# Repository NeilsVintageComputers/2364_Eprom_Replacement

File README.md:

# 2364_Eprom_Replacement

These adapters mount a smd eeprom, AT28C64B, on a pcb that fits and plugs into the 24-pin 2364 footprint. It is much narrower than all the other adapters I have seen (only as wide as the 2364 socket) which allows them to fit side by side in closely spaced sockets like in the IBM 5150.

The programming adapters that are required to program the eeprom board have a 28 or 32 pin header to plug into a eprom programmer.

The only difference in the two versions is the number of pins on the programming adapter, one has 32 pins which is the number of pins on the smd version of the AT28C64B, the other has 28 pins which is the number of pins on the dil version of the AT28C64.  
Choose which ever version will suit your eprom programmer, if the programmer supports the 32-pin SMD version build the 32-pin adapter or if it only supports the 28-pin throughhole version then build the 28-pin adapter.

The jumpers on the rear should be OPEN when programming the device, CLOSED for use in normal read mode.
The "A" and "B" (Which is NOT a jumper) on the eeprom board should be connected to "A" and "B" on the programmer board.

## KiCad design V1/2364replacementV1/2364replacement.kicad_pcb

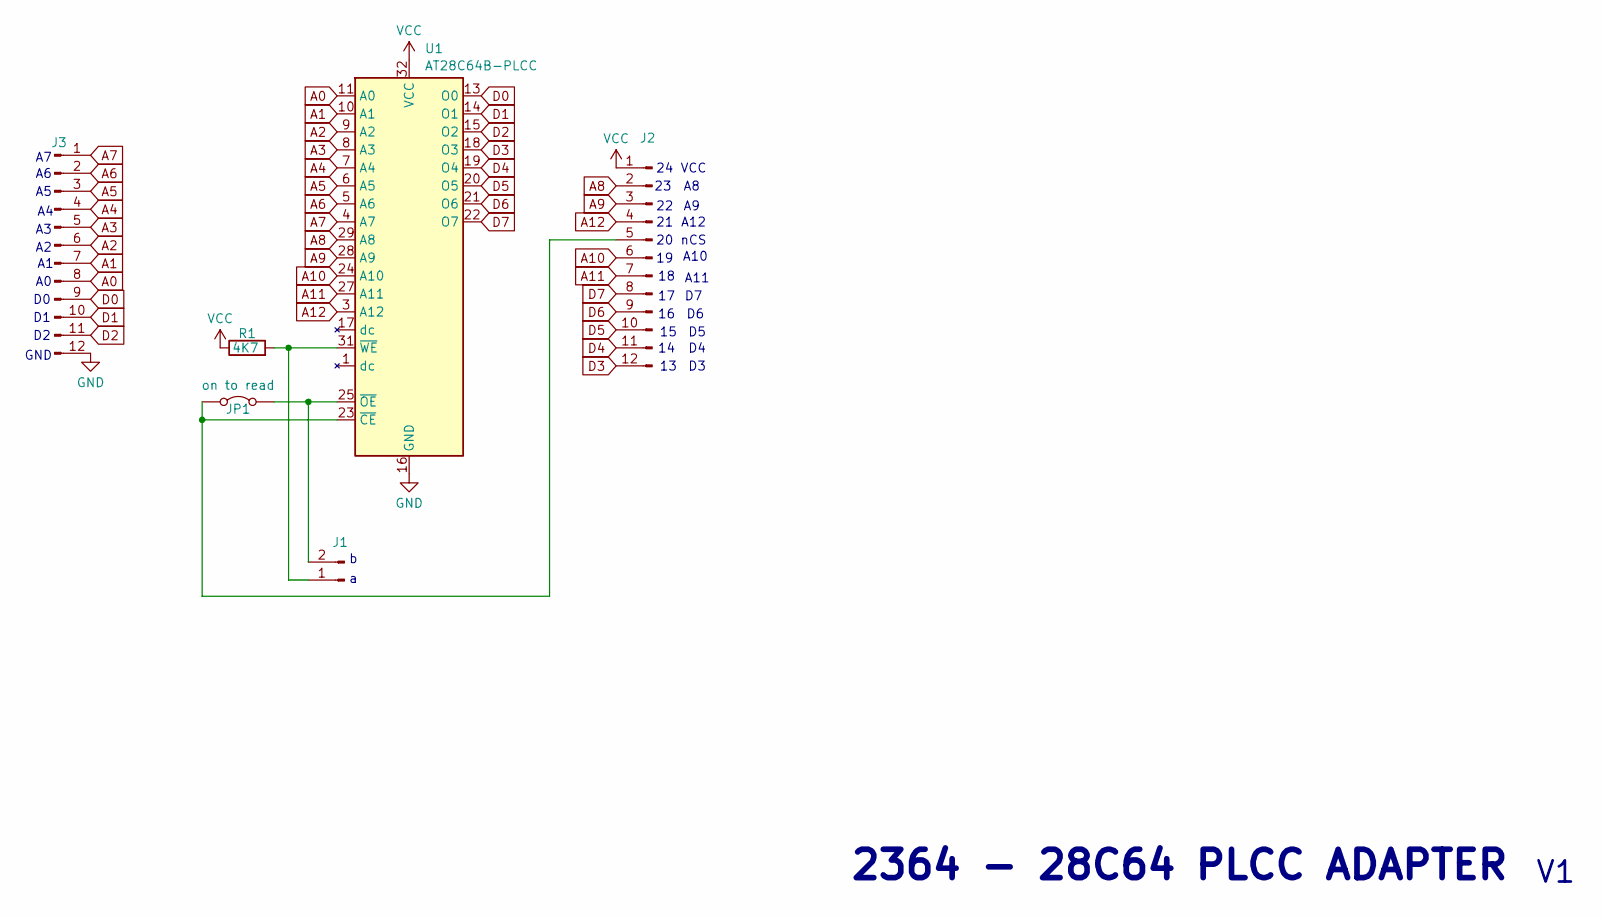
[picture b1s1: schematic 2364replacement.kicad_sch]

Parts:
J1: Conn_01x02_Pin; PinHeader_1x02_P2.54mm_Vertical
J2, J3: Conn_01x12_Pin; PinHeader_1x12_P2.54mm_Vertical
JP1: on to read; PinHeader_1x02_P2.54mm_Vertical
R1: 4K7; R_Axial_DIN0207_L6.3mm_D2.5mm_P10.16mm_Horizontal
U1: AT28C64B-PLCC; PLCC-32_11.4x14.0mm_P1.27mm

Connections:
A0: J3.8, U1.11 (A0)
A1: J3.7, U1.10 (A1)
A2: J3.6, U1.9 (A2)
A3: J3.5, U1.8 (A3)
A4: J3.4, U1.7 (A4)
A5: J3.3, U1.6 (A5)
A6: J3.2, U1.5 (A6)
A7: J3.1, U1.4 (A7)
A8: J2.2, U1.29 (A8)
A9: J2.3, U1.28 (A9)
A10: J2.6, U1.24 (A10)
A11: J2.7, U1.27 (A11)
A12: J2.4, U1.3 (A12)
D0: J3.9, U1.13 (O0)
D1: J3.10, U1.14 (O1)
D2: J3.11, U1.15 (O2)
D3: J2.12, U1.18 (O3)
D4: J2.11, U1.19 (O4)
D5: J2.10, U1.20 (O5)
D6: J2.9, U1.21 (O6)
D7: J2.8, U1.22 (O7)
GND: J3.12, U1.16 (GND)
unnamed: J2.5, JP1.1 (A), U1.23 (~CE)
unnamed: J1.1, R1.2, U1.31 (~WE)
unnamed: J1.2, JP1.2 (B), U1.25 (~OE)
VCC: J2.1, R1.1, U1.32 (VCC)

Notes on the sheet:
VCC
A12
nCS
A10
2364 - 28C64 PLCC ADAPTER
A11
GND

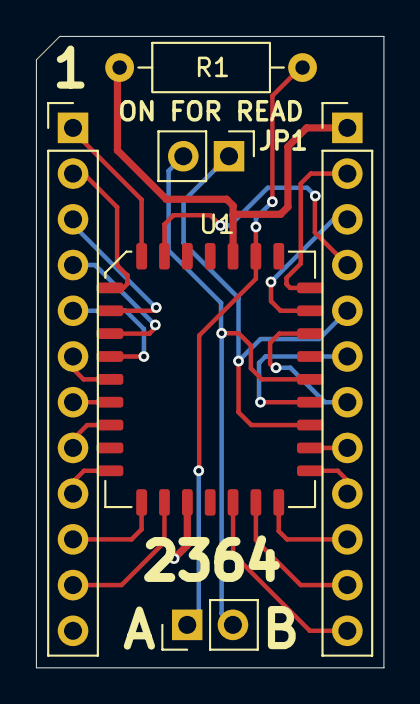
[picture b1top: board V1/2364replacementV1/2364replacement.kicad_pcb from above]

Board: 2 copper layers, 19.3 x 35.1 mm, 6 parts (0 on the bottom side), 26 nets.

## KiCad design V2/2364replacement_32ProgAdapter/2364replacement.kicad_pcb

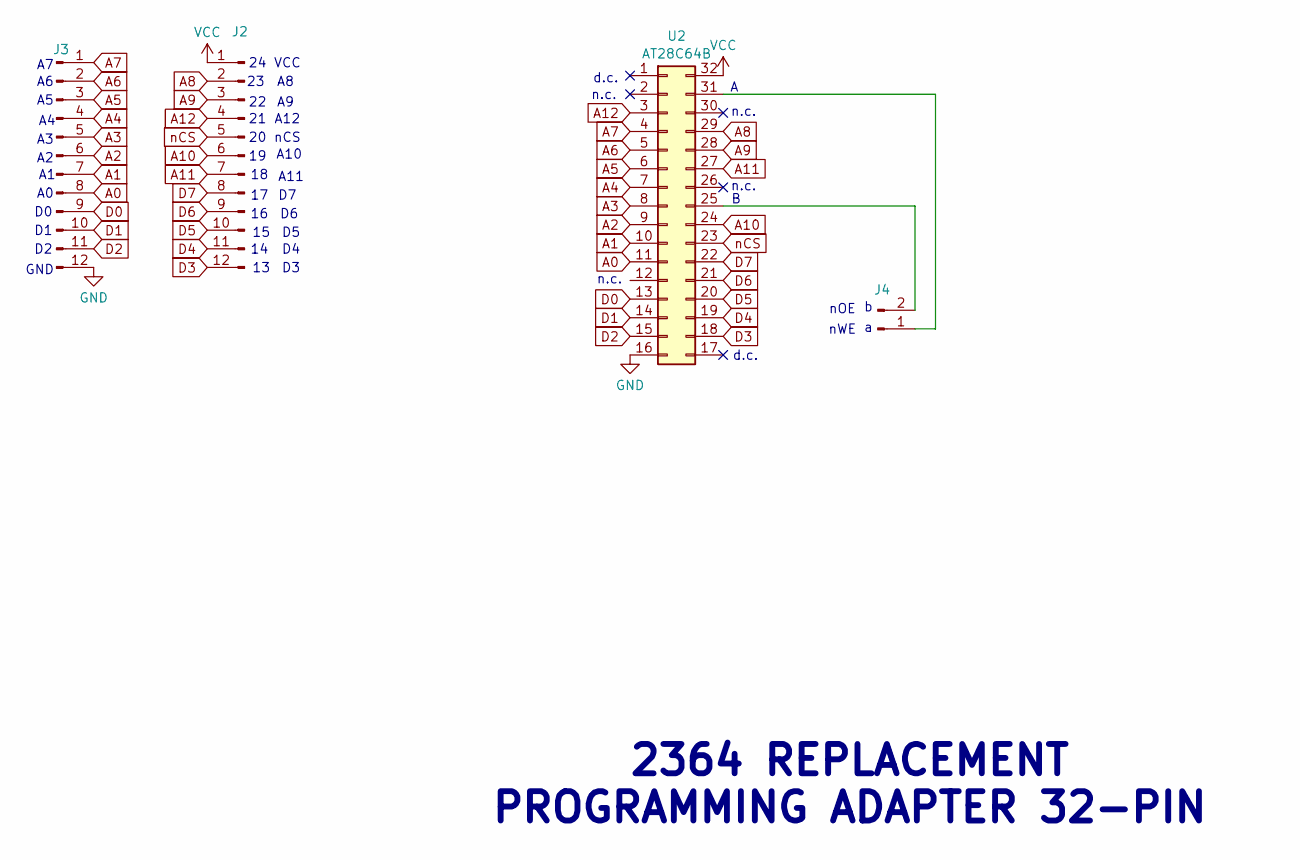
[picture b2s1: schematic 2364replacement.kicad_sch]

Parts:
J2, J3: Conn_01x12_Pin; PinHeader_1x12_P2.54mm_Vertical
J4: Conn_01x02_Pin; PinHeader_1x02_P2.54mm_Vertical
U2: AT28C64B; DIP-32_W15.24mm_LongPads

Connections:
A0: J3.8, U2.11
A1: J3.7, U2.10
A2: J3.6, U2.9
A3: J3.5, U2.8
A4: J3.4, U2.7
A5: J3.3, U2.6
A6: J3.2, U2.5
A7: J3.1, U2.4
A8: J2.2, U2.29
A9: J2.3, U2.28
A10: J2.6, U2.24
A11: J2.7, U2.27
A12: J2.4, U2.3
D0: J3.9, U2.13
D1: J3.10, U2.14
D2: J3.11, U2.15
D3: J2.12, U2.18
D4: J2.11, U2.19
D5: J2.10, U2.20
D6: J2.9, U2.21
D7: J2.8, U2.22
GND: J3.12, U2.16
unnamed: J4.1, U2.31
unnamed: J4.2, U2.25
VCC: J2.1, U2.32
nCS: J2.5, U2.23

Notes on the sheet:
VCC
n.c.
nOE
A12
nWE
nCS
d.c.
2364 REPLACEMENT PROGRAMMING ADAPTER 32-PIN
A10
A11
GND

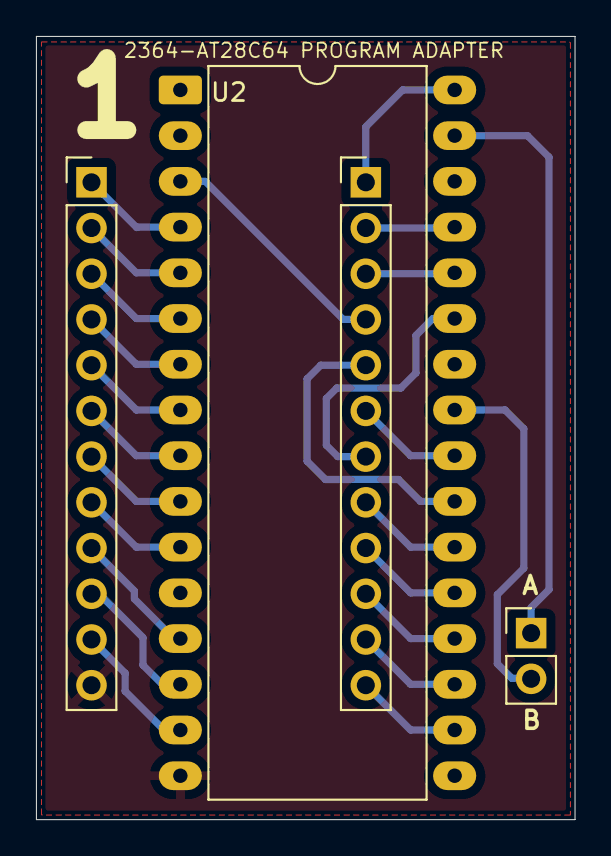
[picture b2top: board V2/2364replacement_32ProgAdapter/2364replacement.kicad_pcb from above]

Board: 2 copper layers, 29.9 x 43.5 mm, 4 parts (0 on the bottom side), 26 nets.

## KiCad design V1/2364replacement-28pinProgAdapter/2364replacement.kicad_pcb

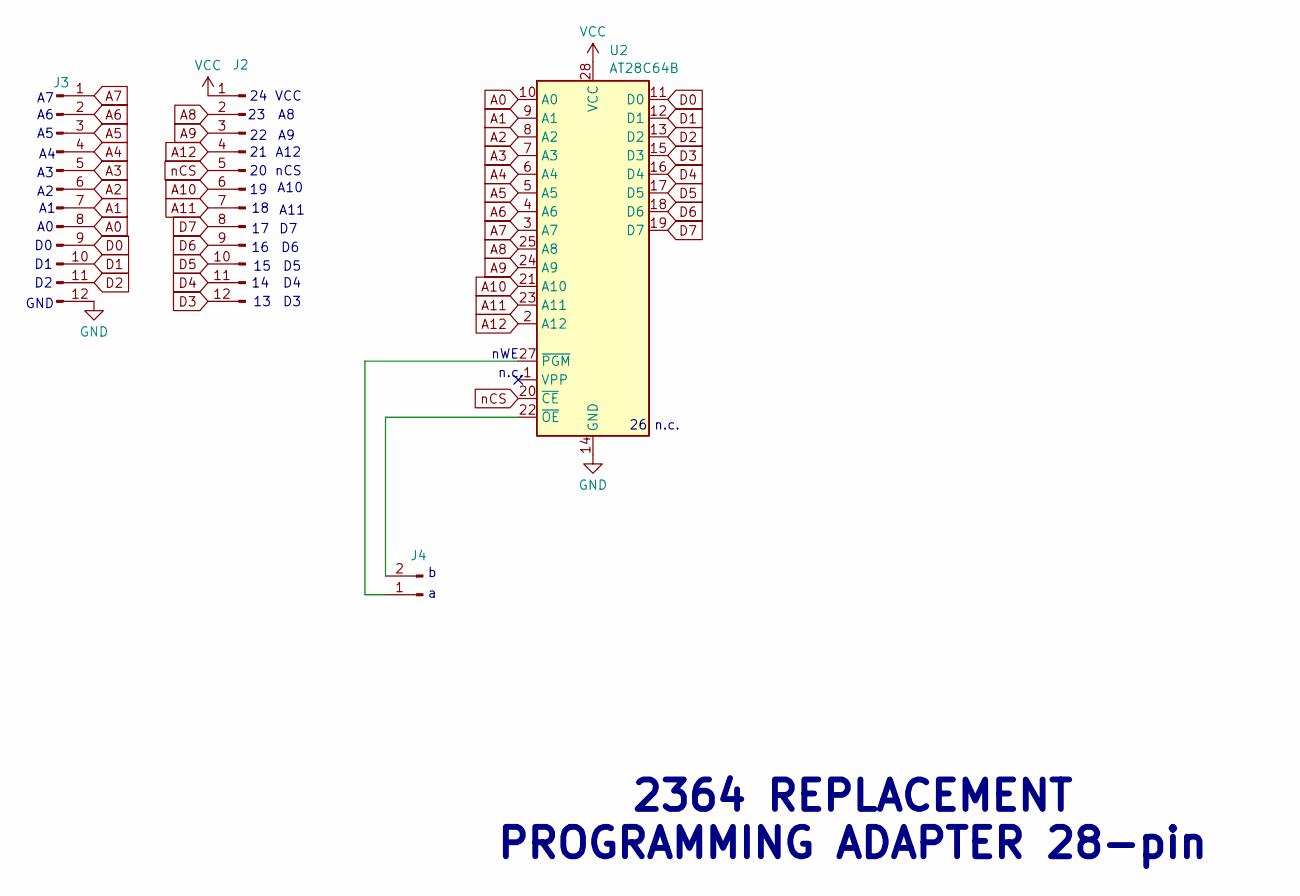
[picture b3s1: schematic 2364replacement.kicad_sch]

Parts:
J2, J3: Conn_01x12_Pin; PinHeader_1x12_P2.54mm_Vertical
J4: Conn_01x02_Pin; PinHeader_1x02_P2.54mm_Vertical
U2: AT28C64B; DIP-28_W15.24mm

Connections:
A0: J3.8, U2.10 (A0)
A1: J3.7, U2.9 (A1)
A2: J3.6, U2.8 (A2)
A3: J3.5, U2.7 (A3)
A4: J3.4, U2.6 (A4)
A5: J3.3, U2.5 (A5)
A6: J3.2, U2.4 (A6)
A7: J3.1, U2.3 (A7)
A8: J2.2, U2.25 (A8)
A9: J2.3, U2.24 (A9)
A10: J2.6, U2.21 (A10)
A11: J2.7, U2.23 (A11)
A12: J2.4, U2.2 (A12)
D0: J3.9, U2.11 (D0)
D1: J3.10, U2.12 (D1)
D2: J3.11, U2.13 (D2)
D3: J2.12, U2.15 (D3)
D4: J2.11, U2.16 (D4)
D5: J2.10, U2.17 (D5)
D6: J2.9, U2.18 (D6)
D7: J2.8, U2.19 (D7)
GND: J3.12, U2.14 (GND)
unnamed: J4.1, U2.27 (~PGM)
unnamed: J4.2, U2.22 (~OE)
VCC: J2.1, U2.28 (VCC)
nCS: J2.5, U2.20 (~CE)

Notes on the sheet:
VCC
n.c.
A12
nWE
nCS
26 n.c.
2364 REPLACEMENT PROGRAMMING ADAPTER 28-pin
A10
A11
GND

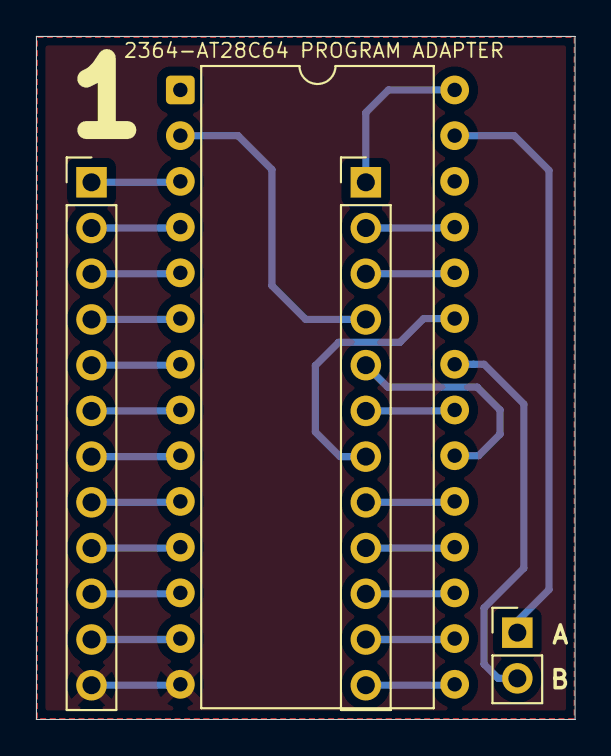
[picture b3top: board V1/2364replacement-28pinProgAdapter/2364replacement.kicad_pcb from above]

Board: 2 copper layers, 29.9 x 37.9 mm, 4 parts (0 on the bottom side), 26 nets.
